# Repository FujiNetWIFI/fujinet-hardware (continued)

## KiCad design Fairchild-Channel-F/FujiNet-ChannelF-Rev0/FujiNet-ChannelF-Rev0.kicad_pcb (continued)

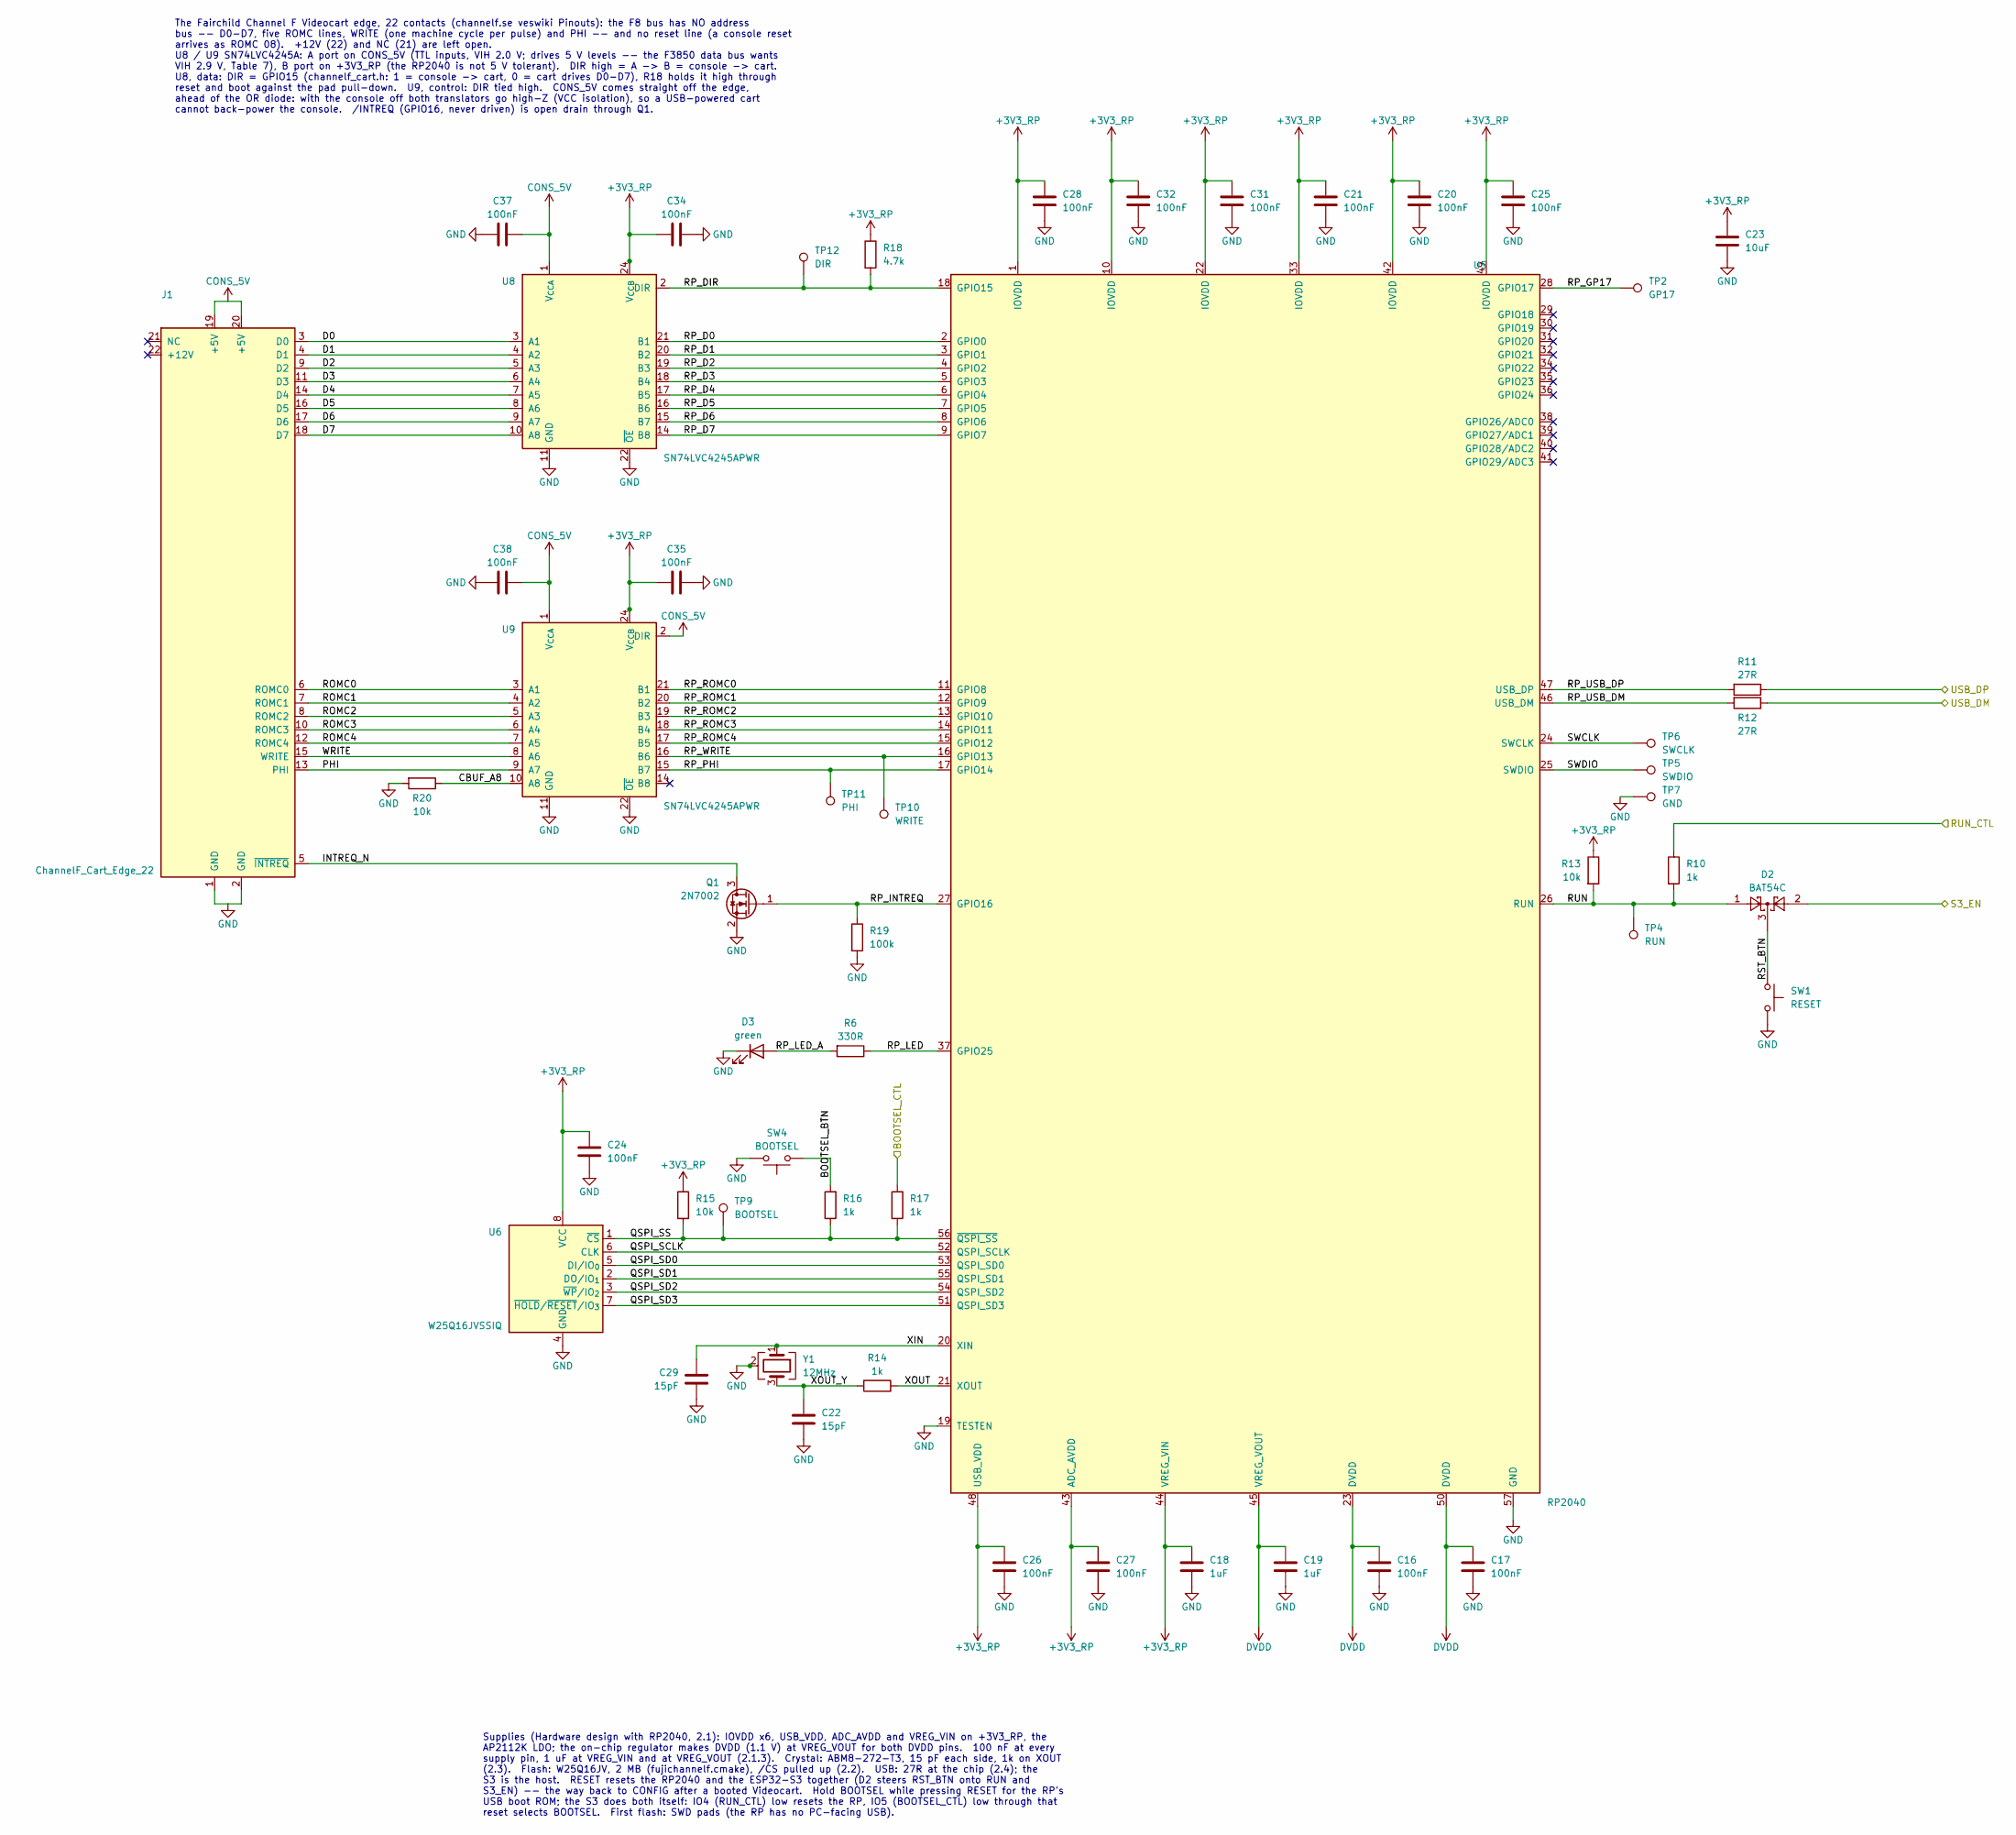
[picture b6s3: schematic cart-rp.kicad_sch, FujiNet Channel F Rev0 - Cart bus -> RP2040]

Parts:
C16, C17, C20, C21, C24, C25, C26, C27, C28, C31, C32, C34, C35, C37, C38: 100nF; C_0603_1608Metric; MPN CC0603KRX7R9BB104; LCSC C14663
C18, C19: 1uF; C_0603_1608Metric; MPN CL10A105KB8NNNC; LCSC C15849
C22, C29: 15pF; C_0603_1608Metric; MPN CL10C150JB8NNNC; LCSC C1644
C23: 10uF; C_0603_1608Metric; MPN CL10A106KP8NNNC; LCSC C19702
D2: BAT54C; SOT-23; MPN BAT54C,215; LCSC C37704
D3: green; LED_0603_1608Metric; MPN KT-0603G; LCSC C12624
J1: ChannelF_Cart_Edge_22; ChannelF_Videocart_Edge_22
Q1: 2N7002; SOT-23; MPN 2N7002; LCSC C8545
R6: 330R; R_0603_1608Metric; MPN 0603WAF3300T5E; LCSC C23138
R10, R14, R16, R17: 1k; R_0603_1608Metric; MPN 0603WAF1001T5E; LCSC C21190
R11, R12: 27R; R_0603_1608Metric; MPN 0603WAF270JT5E; LCSC C25190
R13, R15, R20: 10k; R_0603_1608Metric; MPN 0603WAF1002T5E; LCSC C25804
R18: 4.7k; R_0603_1608Metric; MPN 0603WAF4701T5E; LCSC C23162
R19: 100k; R_0603_1608Metric; MPN 0603WAF1003T5E; LCSC C25803
SW1: RESET; SW_SPST_TL3342; MPN TL3342F160QG; LCSC C2886898
SW4: BOOTSEL; SW_SPST_TL3342; MPN TL3342F160QG; LCSC C2886898
TP2: GP17; TestPoint_Pad_D1.5mm
TP4: RUN; TestPoint_Pad_D1.5mm
TP5: SWDIO; TestPoint_Pad_D1.5mm
TP6: SWCLK; TestPoint_Pad_D1.5mm
TP7: GND; TestPoint_Pad_D1.5mm
TP9: BOOTSEL; TestPoint_Pad_D1.5mm
TP10: WRITE; TestPoint_Pad_D1.5mm
TP11: PHI; TestPoint_Pad_D1.5mm
TP12: DIR; TestPoint_Pad_D1.5mm
U5: RP2040; QFN-56-1EP_7x7mm_P0.4mm_EP3.2x3.2mm; MPN RP2040; LCSC C2040
U6: W25Q16JVSSIQ; SOIC-8_5.3x5.3mm_P1.27mm; MPN W25Q16JVSSIQ; LCSC C82317
U8, U9: SN74LVC4245APWR; TSSOP-24_4.4x7.8mm_P0.65mm; MPN SN74LVC4245APWR; LCSC C7859
Y1: 12MHz; Crystal_SMD_3225-4Pin_3.2x2.5mm; MPN ABM8-272-T3; LCSC C20625731

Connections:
+3V3_RP: C18.1, C20.1, C21.1, C23.1, C24.1, C25.1, C26.1, C27.1, C28.1, C31.1, C32.1, C34.1, C35.1, R13.1, R15.1, R18.1, U5.1 (IOVDD), U5.10 (IOVDD), U5.22 (IOVDD), U5.33 (IOVDD), U5.42 (IOVDD), U5.43 (ADC_AVDD), U5.44 (VREG_VIN), U5.48 (USB_VDD), U5.49 (IOVDD), U6.8 (VCC), U8.23 (V_{CCB}), U8.24 (V_{CCB}), U9.23 (V_{CCB}), U9.24 (V_{CCB}); also elsewhere on the board
/BOOTSEL_CTL: R17.1; also elsewhere on the board
/RUN_CTL: R10.1; also elsewhere on the board
/S3_EN: D2.2; also elsewhere on the board
/USB_DM: R12.1; also elsewhere on the board
/USB_DP: R11.1; also elsewhere on the board
/cart-rp/BOOTSEL_BTN: R16.2, SW4.1
/cart-rp/CBUF_A8: R20.1, U9.10 (A8)
/cart-rp/D0: J1.3 (D0), U8.3 (A1)
/cart-rp/D1: J1.4 (D1), U8.4 (A2)
/cart-rp/D2: J1.9 (D2), U8.5 (A3)
/cart-rp/D3: J1.11 (D3), U8.6 (A4)
/cart-rp/D4: J1.14 (D4), U8.7 (A5)
/cart-rp/D5: J1.16 (D5), U8.8 (A6)
/cart-rp/D6: J1.17 (D6), U8.9 (A7)
/cart-rp/D7: J1.18 (D7), U8.10 (A8)
/cart-rp/INTREQ_N: J1.5 (~INTREQ), Q1.3 (D)
/cart-rp/PHI: J1.13 (PHI), U9.9 (A7)
/cart-rp/QSPI_SCLK: U5.52 (QSPI_SCLK), U6.6 (CLK)
/cart-rp/QSPI_SD0: U5.53 (QSPI_SD0), U6.5 (DI/IO_{0})
/cart-rp/QSPI_SD1: U5.55 (QSPI_SD1), U6.2 (DO/IO_{1})
/cart-rp/QSPI_SD2: U5.54 (QSPI_SD2), U6.3 (~WP/IO_{2})
/cart-rp/QSPI_SD3: U5.51 (QSPI_SD3), U6.7 (~HOLD/~RESET/IO_{3})
/cart-rp/QSPI_SS: R15.2, R16.1, R17.2, TP9.1, U5.56 (~QSPI_SS), U6.1 (~CS)
/cart-rp/ROMC0: J1.6 (ROMC0), U9.3 (A1)
/cart-rp/ROMC1: J1.7 (ROMC1), U9.4 (A2)
/cart-rp/ROMC2: J1.8 (ROMC2), U9.5 (A3)
/cart-rp/ROMC3: J1.10 (ROMC3), U9.6 (A4)
/cart-rp/ROMC4: J1.12 (ROMC4), U9.7 (A5)
/cart-rp/RP_D0: U5.2 (GPIO0), U8.21 (B1)
/cart-rp/RP_D1: U5.3 (GPIO1), U8.20 (B2)
/cart-rp/RP_D2: U5.4 (GPIO2), U8.19 (B3)
/cart-rp/RP_D3: U5.5 (GPIO3), U8.18 (B4)
/cart-rp/RP_D4: U5.6 (GPIO4), U8.17 (B5)
/cart-rp/RP_D5: U5.7 (GPIO5), U8.16 (B6)
/cart-rp/RP_D6: U5.8 (GPIO6), U8.15 (B7)
/cart-rp/RP_D7: U5.9 (GPIO7), U8.14 (B8)
/cart-rp/RP_DIR: R18.2, TP12.1, U5.18 (GPIO15), U8.2 (DIR)
/cart-rp/RP_GP17: TP2.1, U5.28 (GPIO17)
/cart-rp/RP_INTREQ: Q1.1 (G), R19.1, U5.27 (GPIO16)
/cart-rp/RP_LED: R6.1, U5.37 (GPIO25)
/cart-rp/RP_LED_A: D3.2 (A), R6.2
/cart-rp/RP_PHI: TP11.1, U5.17 (GPIO14), U9.15 (B7)
/cart-rp/RP_ROMC0: U5.11 (GPIO8), U9.21 (B1)
/cart-rp/RP_ROMC1: U5.12 (GPIO9), U9.20 (B2)
/cart-rp/RP_ROMC2: U5.13 (GPIO10), U9.19 (B3)
/cart-rp/RP_ROMC3: U5.14 (GPIO11), U9.18 (B4)
/cart-rp/RP_ROMC4: U5.15 (GPIO12), U9.17 (B5)
/cart-rp/RP_USB_DM: R12.2, U5.46 (USB_DM)
/cart-rp/RP_USB_DP: R11.2, U5.47 (USB_DP)
/cart-rp/RP_WRITE: TP10.1, U5.16 (GPIO13), U9.16 (B6)
/cart-rp/RST_BTN: D2.3, SW1.1
/cart-rp/RUN: D2.1, R10.2, R13.2, TP4.1, U5.26 (RUN)
/cart-rp/SWCLK: TP6.1, U5.24 (SWCLK)
/cart-rp/SWDIO: TP5.1, U5.25 (SWDIO)
/cart-rp/WRITE: J1.15 (WRITE), U9.8 (A6)
/cart-rp/XIN: C29.1, U5.20 (XIN), Y1.1
/cart-rp/XOUT: R14.1, U5.21 (XOUT)
/cart-rp/XOUT_Y: C22.1, R14.2, Y1.3
CONS_5V: C37.1, C38.1, J1.19 (+5V), J1.20 (+5V), U8.1 (V_{CCA}), U9.1 (V_{CCA}), U9.2 (DIR); also elsewhere on the board
DVDD: C16.1, C17.1, C19.1, U5.23 (DVDD), U5.45 (VREG_VOUT), U5.50 (DVDD)
GND: C16.2, C17.2, C18.2, C19.2, C20.2, C21.2, C22.2, C23.2, C24.2, C25.2, C26.2, C27.2, C28.2, C29.2, C31.2, C32.2, C34.2, C35.2, C37.2, C38.2, D3.1 (K), J1.1 (GND), J1.2 (GND), Q1.2 (S), R19.2, R20.2, SW1.2, SW4.2, TP7.1, U5.19 (TESTEN), U5.57 (GND), U6.4 (GND), U8.11 (GND), U8.12 (GND), U8.13 (GND), U8.22 (~OE), U9.11 (GND), U9.12 (GND), U9.13 (GND), U9.22 (~OE), Y1.2 (G), Y1.4 (G); also elsewhere on the board

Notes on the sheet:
The Fairchild Channel F Videocart edge, 22 contacts (channelf.se veswiki Pinouts): the F8 bus has NO address bus -- D0-D7, five ROMC lines, WRITE (one machine cycle per pulse) and PHI -- and no reset line (a console reset arrives as ROMC 08). +12V (22) and NC (21) are left open. U8 / U9 SN74LVC4245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
Supplies (Hardware design with RP2040, 2.1): IOVDD x6, USB_VDD, ADC_AVDD and VREG_VIN on +3V3_RP, the AP2112K LDO; the on-chip regulator makes DVDD (1.1 V) at VREG_VOUT for both DVDD pins. 100 nF at every supply pin, 1 uF at VREG_VIN and at VREG_VOUT (2.1.3). Crystal: ABM8-272-T3, 15 pF each side, 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

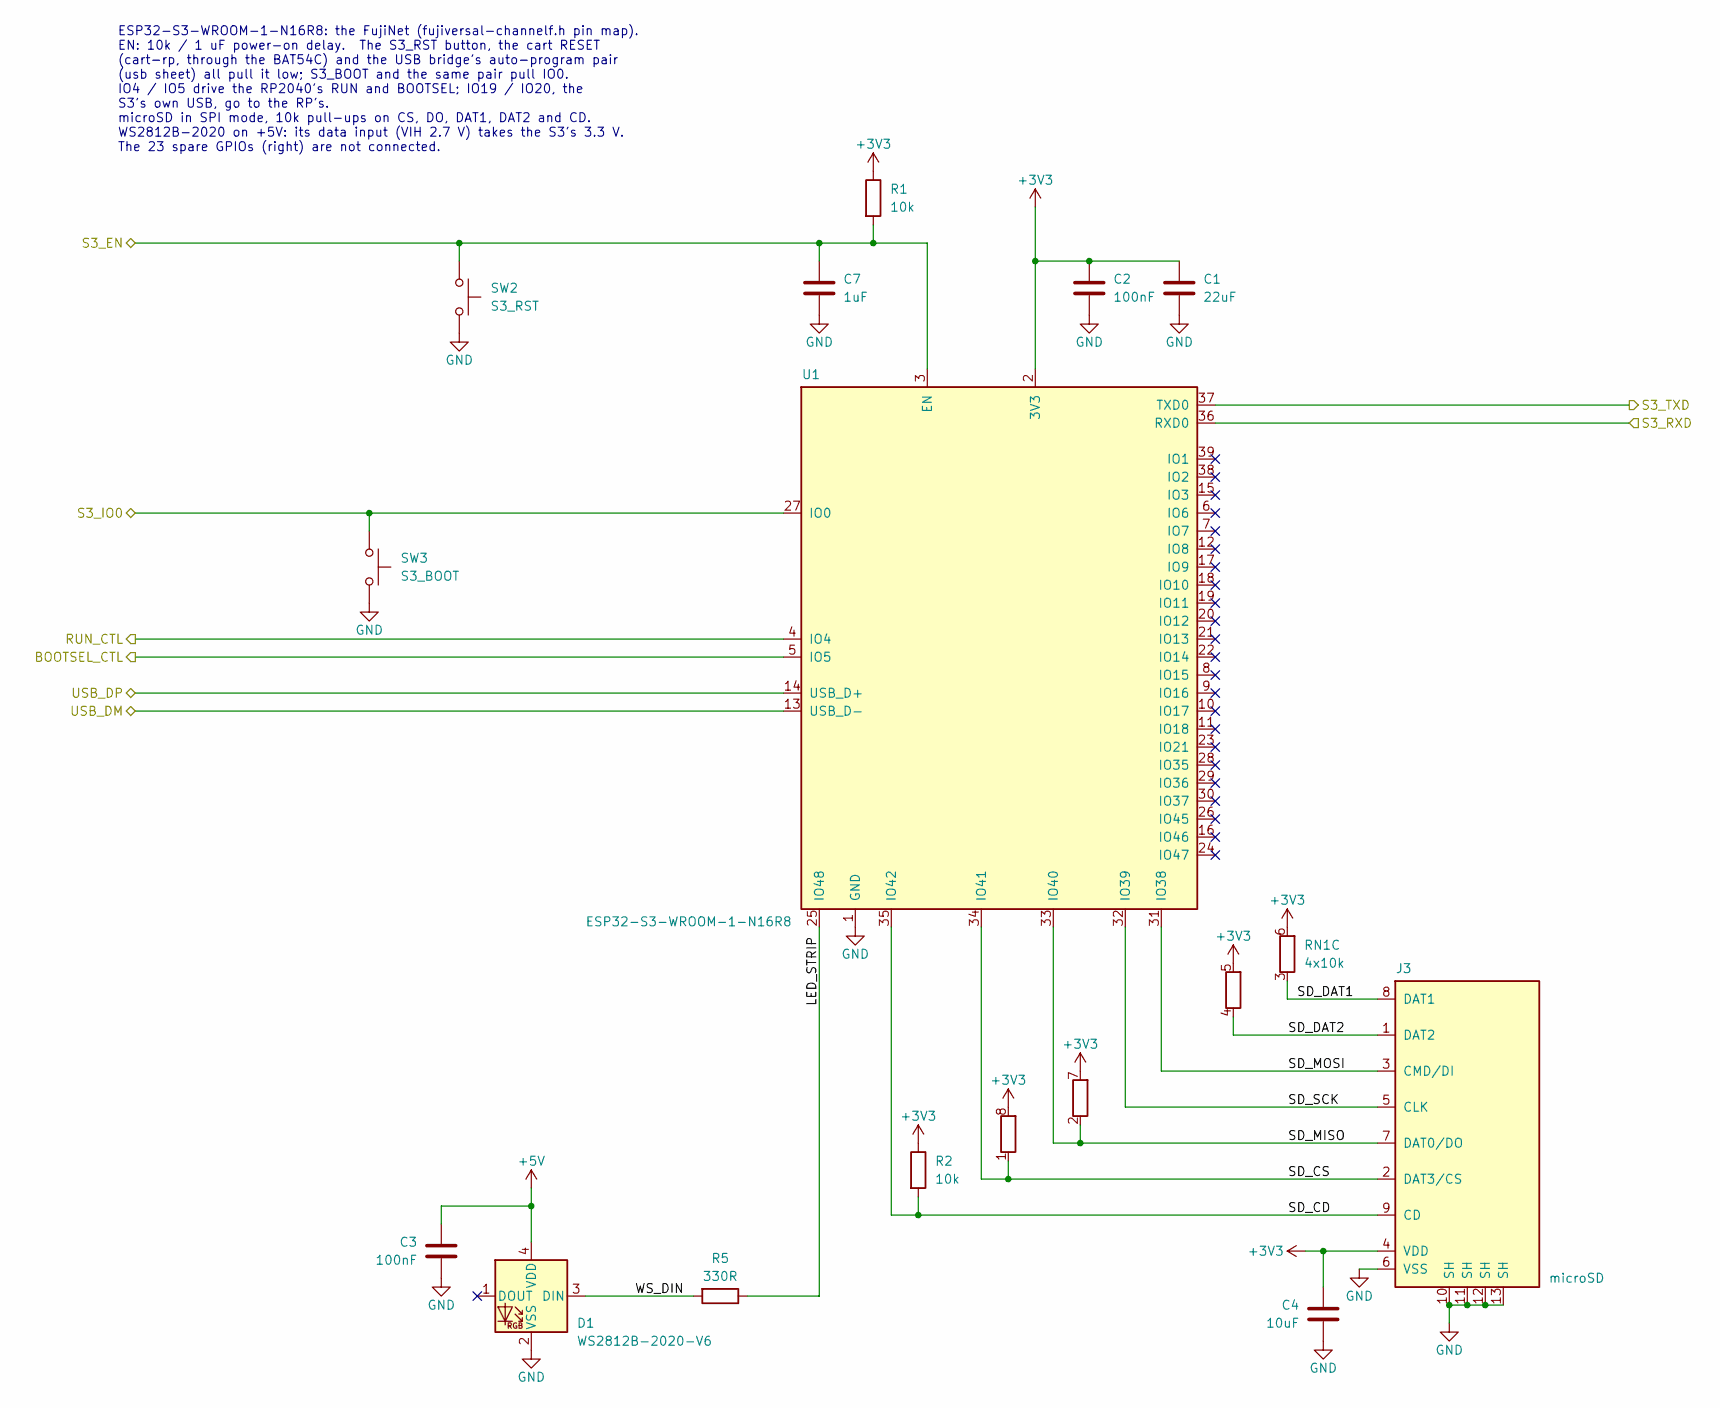
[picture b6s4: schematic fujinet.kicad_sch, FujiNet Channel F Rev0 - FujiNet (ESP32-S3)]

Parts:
C1: 22uF; C_0805_2012Metric; MPN CL21A226MAQNNNE; LCSC C45783
C2, C3: 100nF; C_0603_1608Metric; MPN CC0603KRX7R9BB104; LCSC C14663
C4: 10uF; C_0603_1608Metric; MPN CL10A106KP8NNNC; LCSC C19702
C7: 1uF; C_0603_1608Metric; MPN CL10A105KB8NNNC; LCSC C15849
D1: WS2812B-2020-V6; LED_WS2812B-2020_PLCC4_2.0x2.0mm; MPN WS2812B-2020-V6; LCSC C52917434
J3: microSD; TF-SMD_TF-015; MPN TF-015; LCSC C113206
R1, R2: 10k; R_0603_1608Metric; MPN 0603WAF1002T5E; LCSC C25804
R5: 330R; R_0603_1608Metric; MPN 0603WAF3300T5E; LCSC C23138
RN1: 4x10k; R_Array_Convex_4x0603; MPN 4D03WGJ0103T5E; LCSC C29718
SW2: S3_RST; SW_SPST_TL3342; MPN TL3342F160QG; LCSC C2886898
SW3: S3_BOOT; SW_SPST_TL3342; MPN TL3342F160QG; LCSC C2886898
U1: ESP32-S3-WROOM-1-N16R8; ESP32-S3-WROOM-1; MPN ESP32-S3-WROOM-1-N16R8; LCSC C2913202

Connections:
+3V3: C1.1, C2.1, C4.1, J3.4 (VDD), R1.1, R2.1, RN1.5 (R4.2), RN1.6 (R3.2), RN1.7 (R2.2), RN1.8 (R1.2), U1.2 (3V3); also elsewhere on the board
+5V: C3.1, D1.4 (VDD); also elsewhere on the board
/BOOTSEL_CTL: U1.5 (IO5); also elsewhere on the board
/RUN_CTL: U1.4 (IO4); also elsewhere on the board
/S3_EN: C7.1, R1.2, SW2.1, U1.3 (EN); also elsewhere on the board
/S3_IO0: SW3.1, U1.27 (IO0); also elsewhere on the board
/S3_RXD: U1.36 (RXD0); also elsewhere on the board
/S3_TXD: U1.37 (TXD0); also elsewhere on the board
/USB_DM: U1.13 (USB_D-); also elsewhere on the board
/USB_DP: U1.14 (USB_D+); also elsewhere on the board
/fujinet/LED_STRIP: R5.1, U1.25 (IO48)
/fujinet/SD_CD: J3.9 (CD), R2.2, U1.35 (IO42)
/fujinet/SD_CS: J3.2 (DAT3/CS), RN1.1 (R1.1), U1.34 (IO41)
/fujinet/SD_DAT1: J3.8 (DAT1), RN1.3 (R3.1)
/fujinet/SD_DAT2: J3.1 (DAT2), RN1.4 (R4.1)
/fujinet/SD_MISO: J3.7 (DAT0/DO), RN1.2 (R2.1), U1.33 (IO40)
/fujinet/SD_MOSI: J3.3 (CMD/DI), U1.31 (IO38)
/fujinet/SD_SCK: J3.5 (CLK), U1.32 (IO39)
/fujinet/WS_DIN: D1.3 (DIN), R5.2
GND: C1.2, C2.2, C3.2, C4.2, C7.2, D1.2 (VSS), J3.6 (VSS), J3.10 (SH), J3.11 (SH), J3.12 (SH), J3.13 (SH), SW2.2, SW3.2, U1.1 (GND), U1.40 (GND), U1.41 (GND); also elsewhere on the board

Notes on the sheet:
ESP32-S3-WROOM-1-N16R8: the FujiNet (fujiversal-channelf.h pin map). EN: 10k / 1 uF power-on delay. The S3_RST button, the cart RESET (cart-rp, through the BAT54C) and the USB bridge's auto-program pair (usb sheet) all pull it low; S3_BOOT and the same pair pull IO0. IO4 / IO5 drive the RP2040's RU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

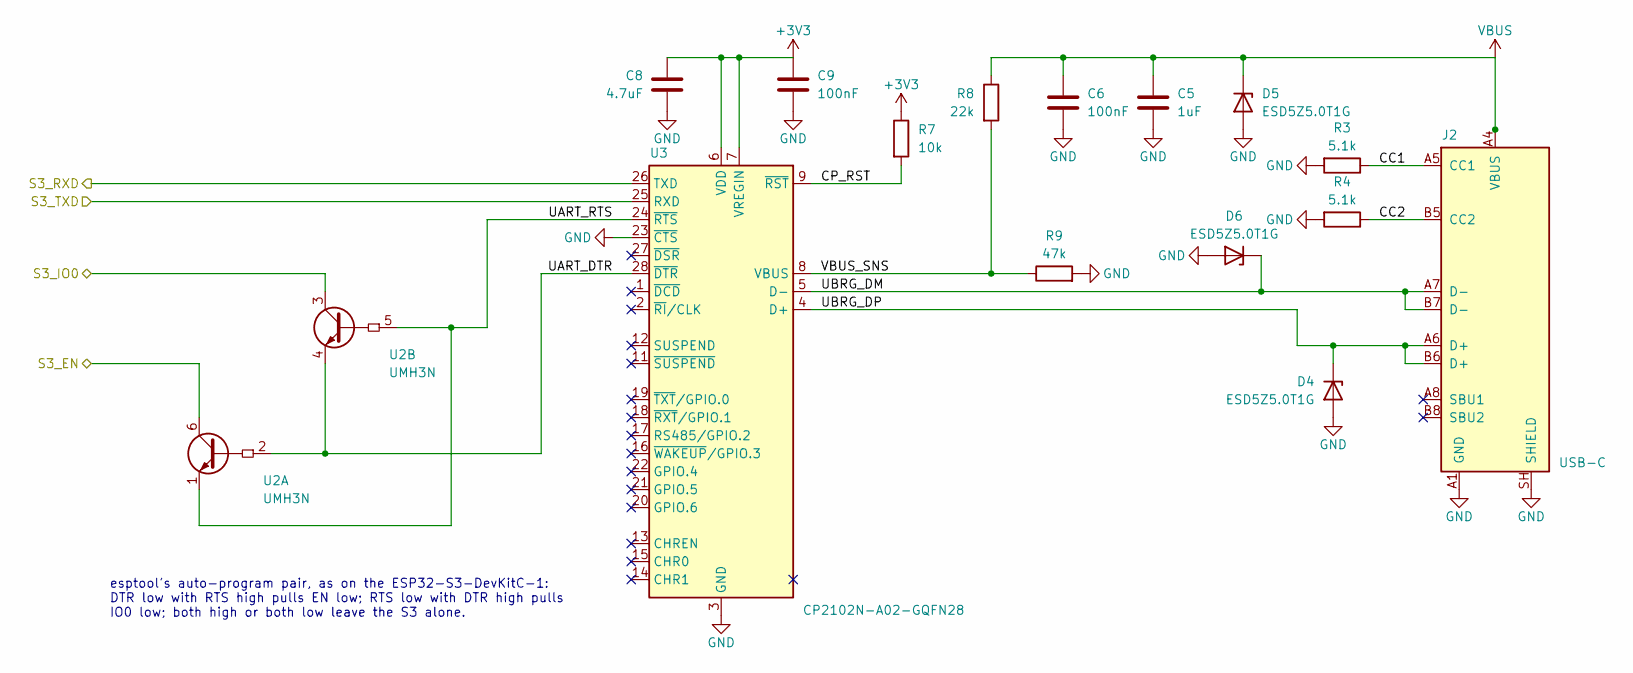
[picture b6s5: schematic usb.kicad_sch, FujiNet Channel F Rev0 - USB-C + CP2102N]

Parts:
C5: 1uF; C_0603_1608Metric; MPN CL10A105KB8NNNC; LCSC C15849
C6, C9: 100nF; C_0603_1608Metric; MPN CC0603KRX7R9BB104; LCSC C14663
C8: 4.7uF; C_0603_1608Metric; MPN CL10A475KO8NNNC; LCSC C19666
D4, D5, D6: ESD5Z5.0T1G; D_SOD-523; MPN ESD5Z5.0T1G; LCSC C82044
J2: USB-C; USB_C_Receptacle_HRO_TYPE-C-31-M-12; MPN TYPE-C-31-M-12; LCSC C165948
R3, R4: 5.1k; R_0603_1608Metric; MPN 0603WAF5101T5E; LCSC C23186
R7: 10k; R_0603_1608Metric; MPN 0603WAF1002T5E; LCSC C25804
R8: 22k; R_0603_1608Metric; MPN 0603WAF2202T5E; LCSC C31850
R9: 47k; R_0603_1608Metric; MPN 0603WAF4702T5E; LCSC C25819
U2: UMH3N; SOT-363_SC-70-6; MPN UMH3N; LCSC C62892
U3: CP2102N-A02-GQFN28; QFN-28-1EP_5x5mm_P0.5mm_EP3.35x3.35mm; MPN CP2102N-A02-GQFN28R; LCSC C964632

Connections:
+3V3: C8.1, C9.1, R7.1, U3.6 (VDD), U3.7 (VREGIN); also elsewhere on the board
/S3_EN: U2.6 (C1); also elsewhere on the board
/S3_IO0: U2.3 (C2); also elsewhere on the board
/S3_RXD: U3.26 (TXD); also elsewhere on the board
/S3_TXD: U3.25 (RXD); also elsewhere on the board
/usb/CC1: J2.A5 (CC1), R3.1
/usb/CC2: J2.B5 (CC2), R4.1
/usb/CP_RST: R7.2, U3.9 (~RST)
/usb/UART_DTR: U2.2 (B1), U2.4 (E2), U3.28 (~DTR)
/usb/UART_RTS: U2.1 (E1), U2.5 (B2), U3.24 (~RTS)
/usb/UBRG_DM: D6.1 (K), J2.A7 (D-), J2.B7 (D-), U3.5 (D-)
/usb/UBRG_DP: D4.1 (K), J2.A6 (D+), J2.B6 (D+), U3.4 (D+)
/usb/VBUS_SNS: R8.2, R9.1, U3.8 (VBUS)
GND: C5.2, C6.2, C8.2, C9.2, D4.2 (A), D5.2 (A), D6.2 (A), J2.A1 (GND), J2.A12 (GND), J2.B1 (GND), J2.B12 (GND), J2.SH (SHIELD), R3.2, R4.2, R9.2, U3.3 (GND), U3.23 (~CTS), U3.29 (GND); also elsewhere on the board
VBUS: C5.1, C6.1, D5.1 (K), J2.A4 (VBUS), J2.A9 (VBUS), J2.B4 (VBUS), J2.B9 (VBUS), R8.1; also elsewhere on the board

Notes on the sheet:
esptool's auto-program pair, as on the ESP32-S3-DevKitC-1: DTR low with RTS high pulls EN low; RTS low with DTR high pulls IO0 low; both high or both low leave the S3 alone.

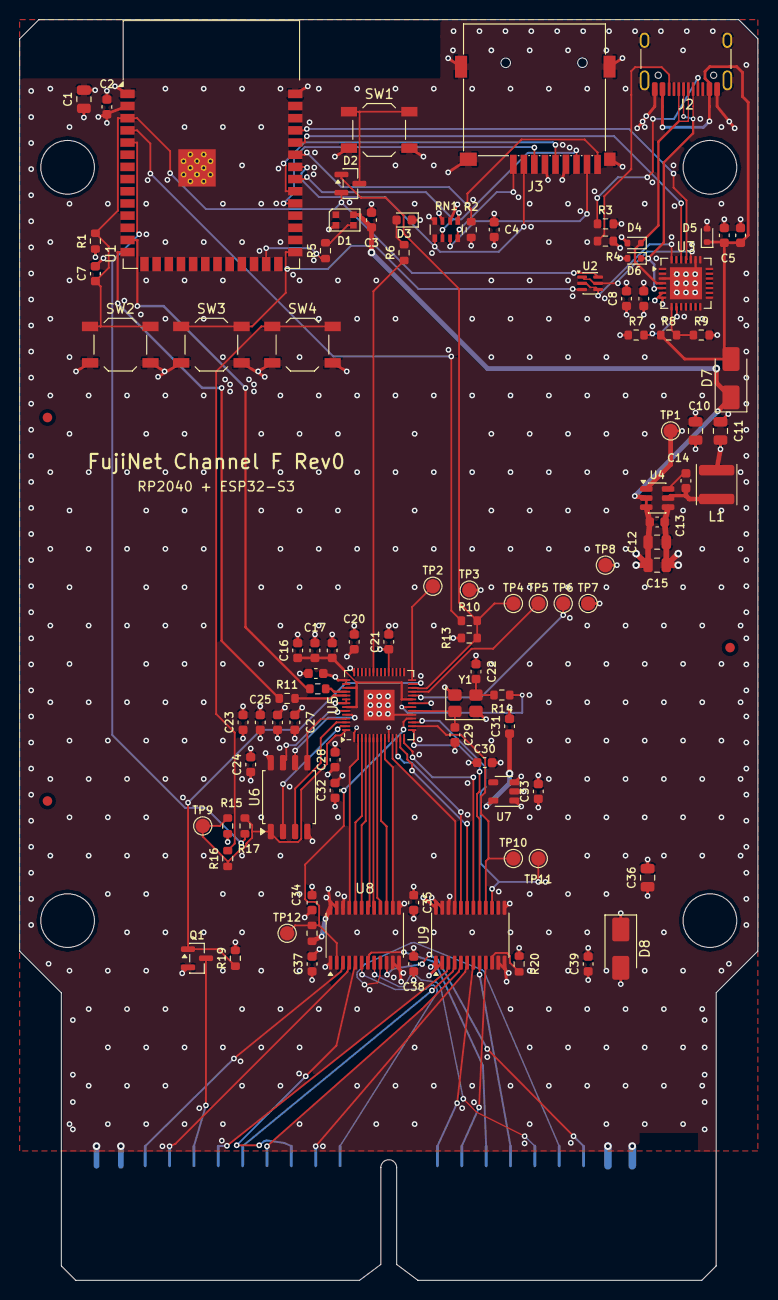
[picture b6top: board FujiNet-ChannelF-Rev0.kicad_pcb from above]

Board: 4 copper layers, 77.0 x 131.5 mm, 106 parts (0 on the bottom side), 87 nets.

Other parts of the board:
FID1, FID2, FID3: Fiducial_1mm_Mask2mm
H1, H2, H3, H4: MountingHole_5.6mm_NPTH

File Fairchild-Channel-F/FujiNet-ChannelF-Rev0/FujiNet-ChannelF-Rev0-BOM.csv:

"Qty","Refs","Value","Footprint","MPN","Manufacturer","LCSC","Description","DNP"
"6","C1,C10,C11,C12,C15,C36","22uF","C_0805_2012Metric","CL21A226MAQNNNE","Samsung Electro-Mechanics","C45783","capacitor (several uses: see schematic)",""
"22","C2,C3,C6,C9,C13,C14,C16,C17,C20,C21,C24,C25,C26,C27,C28,C31,C32,C34,C35,C37,C38,C39","100nF","C_0603_1608Metric","CC0603KRX7R9BB104","YAGEO","C14663","capacitor (several uses: see schematic)",""
"2","C4,C23","10uF","C_0603_1608Metric","CL10A106KP8NNNC","Samsung Electro-Mechanics","C19702","capacitor (several uses: see schematic)",""
"6","C5,C7,C18,C19,C30,C33","1uF","C_0603_1608Metric","CL10A105KB8NNNC","Samsung Electro-Mechanics","C15849","capacitor (several uses: see schematic)",""
"1","C8","4.7uF","C_0603_1608Metric","CL10A475KO8NNNC","Samsung Electro-Mechanics","C19666","CP2102N VDD bulk",""
"2","C22,C29","15pF","C_0603_1608Metric","CL10C150JB8NNNC","Samsung Electro-Mechanics","C1644","crystal load",""
"1","D1","WS2812B-2020-V6","LED_WS2812B-2020_PLCC4_2.0x2.0mm","WS2812B-2020-V6","Worldsemi","C52917434","status LED on +5V (datasheet VDD 3.7-5.3 V; VIH 2.7 V takes 3.3 V data)",""
"1","D2","BAT54C","SOT-23","BAT54C,215","Nexperia","C37704","RESET steering, common cathode",""
"1","D3","green","LED_0603_1608Metric","KT-0603G","Hubei KENTO Elec","C12624","RP activity LED",""
"3","D4,D5,D6","ESD5Z5.0T1G","D_SOD-523","ESD5Z5.0T1G","onsemi","C82044","ESD",""
"2","D7,D8","SS34","D_SMA","SS34","MDD (Microdiode Semiconductor)","C8678","diode (several uses: see schematic)",""
"1","J2","USB-C","USB_C_Receptacle_HRO_TYPE-C-31-M-12","TYPE-C-31-M-12","Korean Hroparts Elec","C165948","power + S3 programming",""
"1","J3","microSD","TF-SMD_TF-015","TF-015","SOFNG","C113206","microSD push-push, SPI mode",""
"1","L1","6.8uH","L_Sunlord_SWPA4030S","SWPA4030S6R8MT","Sunlord","C62684","buck inductor",""
"1","Q1","2N7002","SOT-23","2N7002","Jiangsu Changjing (JSCJ)","C8545","/INTREQ open-drain driver (GP16, unused by the firmware)",""
"6","R1,R2,R7,R13,R15,R20","10k","R_0603_1608Metric","0603WAF1002T5E","UNI-ROYAL","C25804","resistor (several uses: see schematic)",""
"2","R3,R4","5.1k","R_0603_1608Metric","0603WAF5101T5E","UNI-ROYAL","C23186","UFP Rd",""
"2","R5,R6","330R","R_0603_1608Metric","0603WAF3300T5E","UNI-ROYAL","C23138","resistor (several uses: see schematic)",""
"1","R8","22k","R_0603_1608Metric","0603WAF2202T5E","UNI-ROYAL","C31850","VBUS sense divider",""
"1","R9","47k","R_0603_1608Metric","0603WAF4702T5E","UNI-ROYAL","C25819","VBUS sense divider",""
"4","R10,R14,R16,R17","1k","R_0603_1608Metric","0603WAF1001T5E","UNI-ROYAL","C21190","resistor (several uses: see schematic)",""
"2","R11,R12","27R","R_0603_1608Metric","0603WAF270JT5E","UNI-ROYAL","C25190","USB series",""
"1","R18","4.7k","R_0603_1608Metric","0603WAF4701T5E","UNI-ROYAL","C23162","DIR pull-up: console -> cart through RP reset / boot",""
"1","R19","100k","R_0603_1608Metric","0603WAF1003T5E","UNI-ROYAL","C25803","/INTREQ FET gate pull-down",""
"1","RN1","4x10k","R_Array_Convex_4x0603","4D03WGJ0103T5E","UNI-ROYAL","C29718","SD pull-ups",""
"1","SW1","RESET","SW_SPST_TL3342","TL3342F160QG","E-Switch","C2886898","cart RESET: RP RUN + S3 EN via BAT54C",""
"1","SW2","S3_RST","SW_SPST_TL3342","TL3342F160QG","E-Switch","C2886898","ESP32-S3 EN",""
"1","SW3","S3_BOOT","SW_SPST_TL3342","TL3342F160QG","E-Switch","C2886898","ESP32-S3 BOOT (IO0)",""
"1","SW4","BOOTSEL","SW_SPST_TL3342","TL3342F160QG","E-Switch","C2886898","RP2040 BOOTSEL (hold while pressing RESET)",""
"1","U1","ESP32-S3-WROOM-1-N16R8","ESP32-S3-WROOM-1","ESP32-S3-WROOM-1-N16R8","Espressif","C2913202","FujiNet core (fujiversal-channelf)",""
"1","U2","UMH3N","SOT-363_SC-70-6","UMH3N","Jiangsu Changjing (JSCJ)","C62892","esptool auto-program (DevKitC-1 style)",""
"1","U3","CP2102N-A02-GQFN28","QFN-28-1EP_5x5mm_P0.5mm_EP3.35x3.35mm","CP2102N-A02-GQFN28R","Silicon Labs","C964632","USB-UART for S3 flashing/console (self-powered)",""
"1","U4","AP63203WU","TSOT-23-6","AP63203WU-7","Diodes Incorporated","C780769","3.3V 2A buck",""
"1","U5","RP2040","QFN-56-1EP_7x7mm_P0.4mm_EP3.2x3.2mm","RP2040","Raspberry Pi","C2040","F8 bus memory device: ROMC state machine on core1 (fujichannelf)",""
"1","U6","W25Q16JVSSIQ","SOIC-8_5.3x5.3mm_P1.27mm","W25Q16JVSSIQ","Winbond","C82317","2 MB QSPI boot flash",""
"1","U7","AP2112K-3.3","SOT-23-5","AP2112K-3.3TRG1","Diodes Incorporated","C51118","RP2040 + flash + translator B ports 3.3V LDO, fast start",""
"2","U8,U9","SN74LVC4245APWR","TSSOP-24_4.4x7.8mm_P0.65mm","SN74LVC4245APWR","Texas Instruments","C7859","U (several uses: see schematic)",""
"1","Y1","12MHz","Crystal_SMD_3225-4Pin_3.2x2.5mm","ABM8-272-T3","Abracon","C20625731","",""

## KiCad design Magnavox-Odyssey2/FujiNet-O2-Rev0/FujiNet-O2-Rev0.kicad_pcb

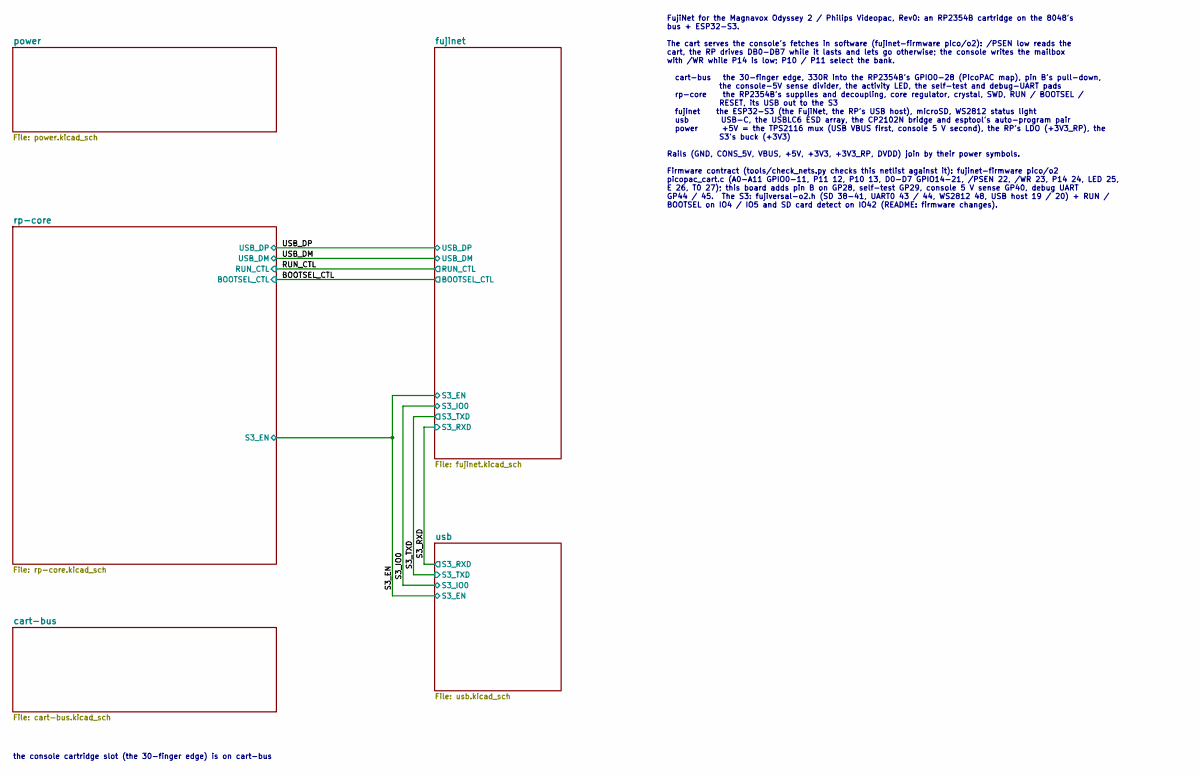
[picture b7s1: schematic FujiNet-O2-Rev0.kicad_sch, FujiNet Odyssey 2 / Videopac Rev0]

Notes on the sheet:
the console cartridge slot (the 30-finger edge) is on cart-bus
FujiNet for the Magnavox Odyssey 2 / Philips Videopac, Rev0: an RP2354B cartridge on the 8048's bus + ESP32-S3. The cart serves the console's fetches in software (fujinet-firmware pico/o2): /PSEN low reads the cart, the RP drives DB0-DB7 while it lasts and lets go otherwise; the console writes the 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

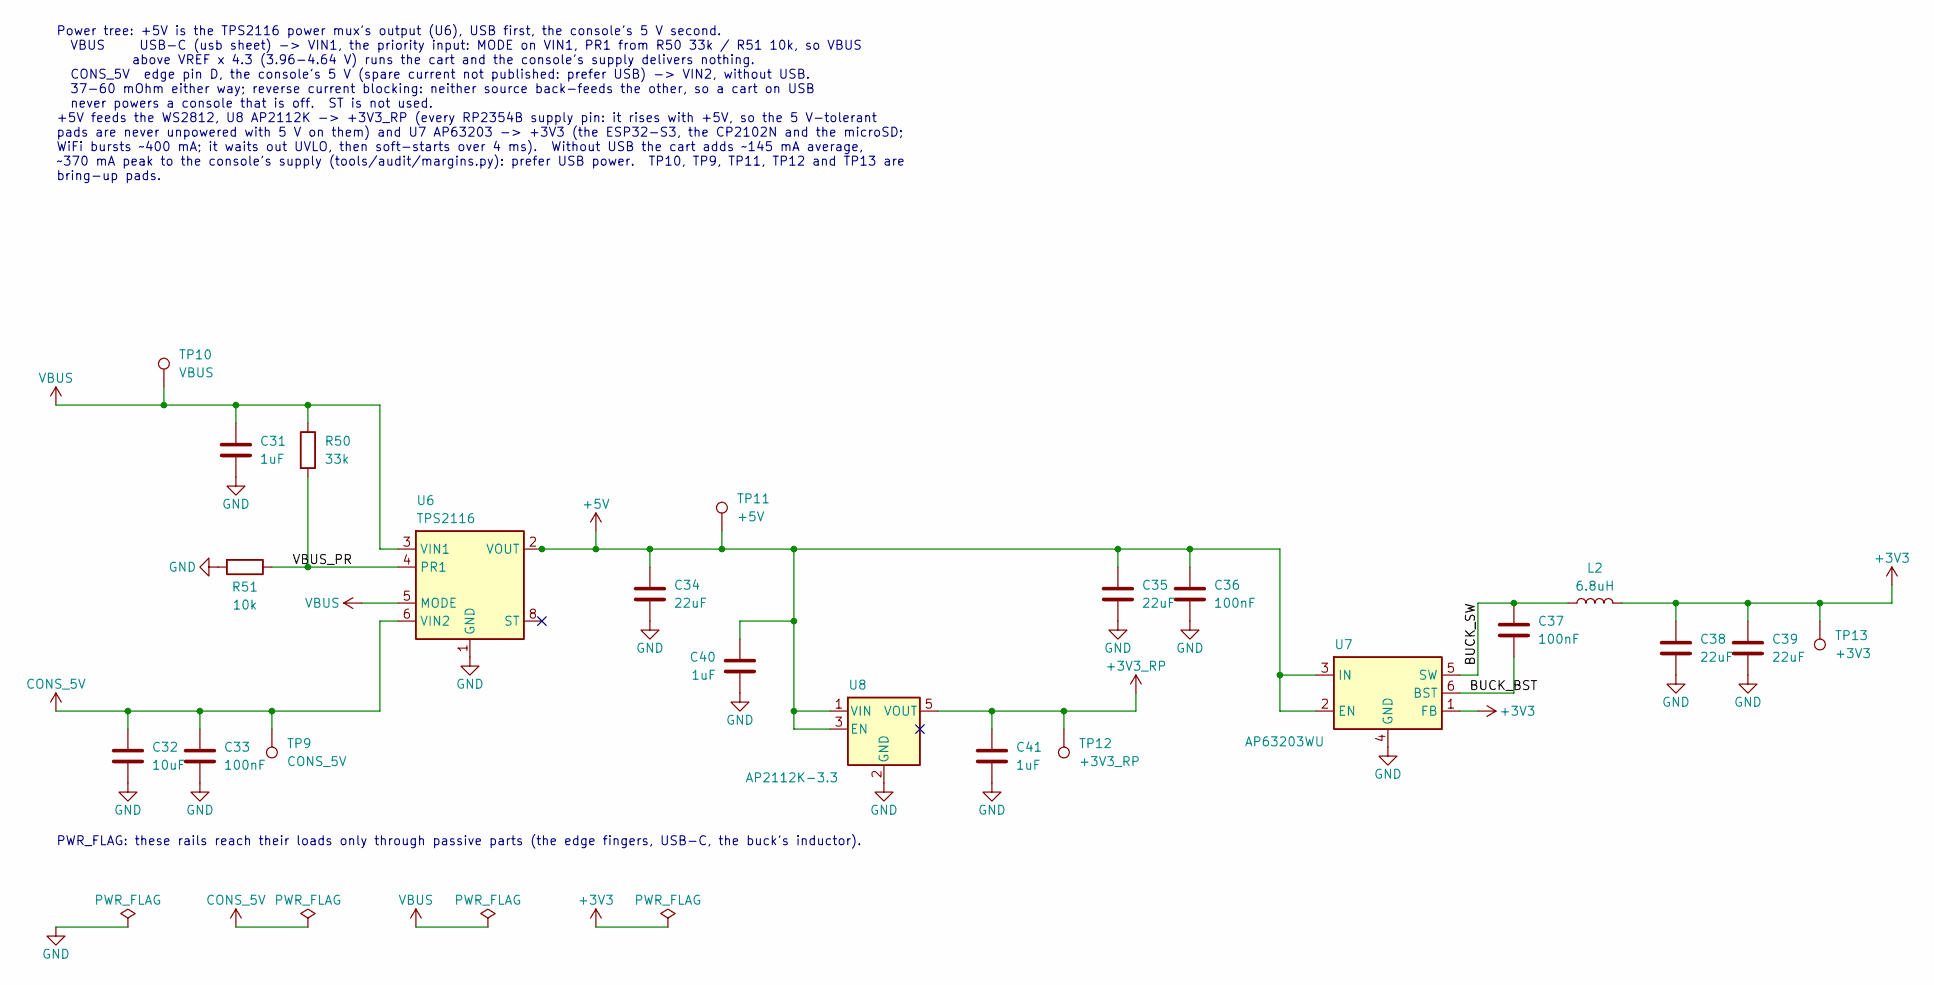
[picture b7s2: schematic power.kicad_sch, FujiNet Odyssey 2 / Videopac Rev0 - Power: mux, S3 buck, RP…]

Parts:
C31, C40, C41: 1uF; C_0603_1608Metric; MPN CL10A105KB8NNNC; LCSC C15849
C32: 10uF; C_0603_1608Metric; MPN CL10A106KP8NNNC; LCSC C19702
C33, C36, C37: 100nF; C_0603_1608Metric; MPN CC0603KRX7R9BB104; LCSC C14663
C34, C35, C38, C39: 22uF; C_0805_2012Metric; MPN CL21A226MAQNNNE; LCSC C45783
L2: 6.8uH; L_Sunlord_SWPA4030S; MPN SWPA4030S6R8MT; LCSC C62684
R50: 33k; R_0603_1608Metric; MPN 0603WAF3302T5E; LCSC C4216
R51: 10k; R_0603_1608Metric; MPN 0603WAF1002T5E; LCSC C25804
TP9: CONS_5V; TestPoint_Pad_D1.5mm
TP10: VBUS; TestPoint_Pad_D1.5mm
TP11: +5V; TestPoint_Pad_D1.5mm
TP12: +3V3_RP; TestPoint_Pad_D1.5mm
TP13: +3V3; TestPoint_Pad_D1.5mm
U6: TPS2116; SOT-583-8; MPN TPS2116DRLR; LCSC C3235557
U7: AP63203WU; TSOT-23-6; MPN AP63203WU-7; LCSC C780769
U8: AP2112K-3.3; SOT-23-5; MPN AP2112K-3.3TRG1; LCSC C51118

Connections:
+3V3: C38.1, C39.1, L2.2, TP13.1, U7.1 (FB); also elsewhere on the board
+3V3_RP: C41.1, TP12.1, U8.5 (VOUT); also elsewhere on the board
+5V: C34.1, C35.1, C36.1, C40.1, TP11.1, U6.2 (VOUT), U6.7 (VOUT), U7.2 (EN), U7.3 (IN), U8.1 (VIN), U8.3 (EN); also elsewhere on the board
/power/BUCK_BST: C37.2, U7.6 (BST)
/power/BUCK_SW: C37.1, L2.1, U7.5 (SW)
/power/VBUS_PR: R50.2, R51.1, U6.4 (PR1)
CONS_5V: C32.1, C33.1, TP9.1, U6.6 (VIN2); also elsewhere on the board
GND: C31.2, C32.2, C33.2, C34.2, C35.2, C36.2, C38.2, C39.2, C40.2, C41.2, R51.2, U6.1 (GND), U7.4 (GND), U8.2 (GND); also elsewhere on the board
VBUS: C31.1, R50.1, TP10.1, U6.3 (VIN1), U6.5 (MODE); also elsewhere on the board

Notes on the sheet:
PWR_FLAG: these rails reach their loads only through passive parts (the edge fingers, USB-C, the buck's inductor).
Power tree: +5V is the TPS2116 power mux's output (U6), USB first, the console's 5 V second. VBUS USB-C (usb sheet) -> VIN1, the priority input: MODE on VIN1, PR1 from R50 33k / R51 10k, so VBUS above VREF x 4.3 (3.96-4.64 V) runs the cart and the console's supply delivers nothing. CONS_5V edge pin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
